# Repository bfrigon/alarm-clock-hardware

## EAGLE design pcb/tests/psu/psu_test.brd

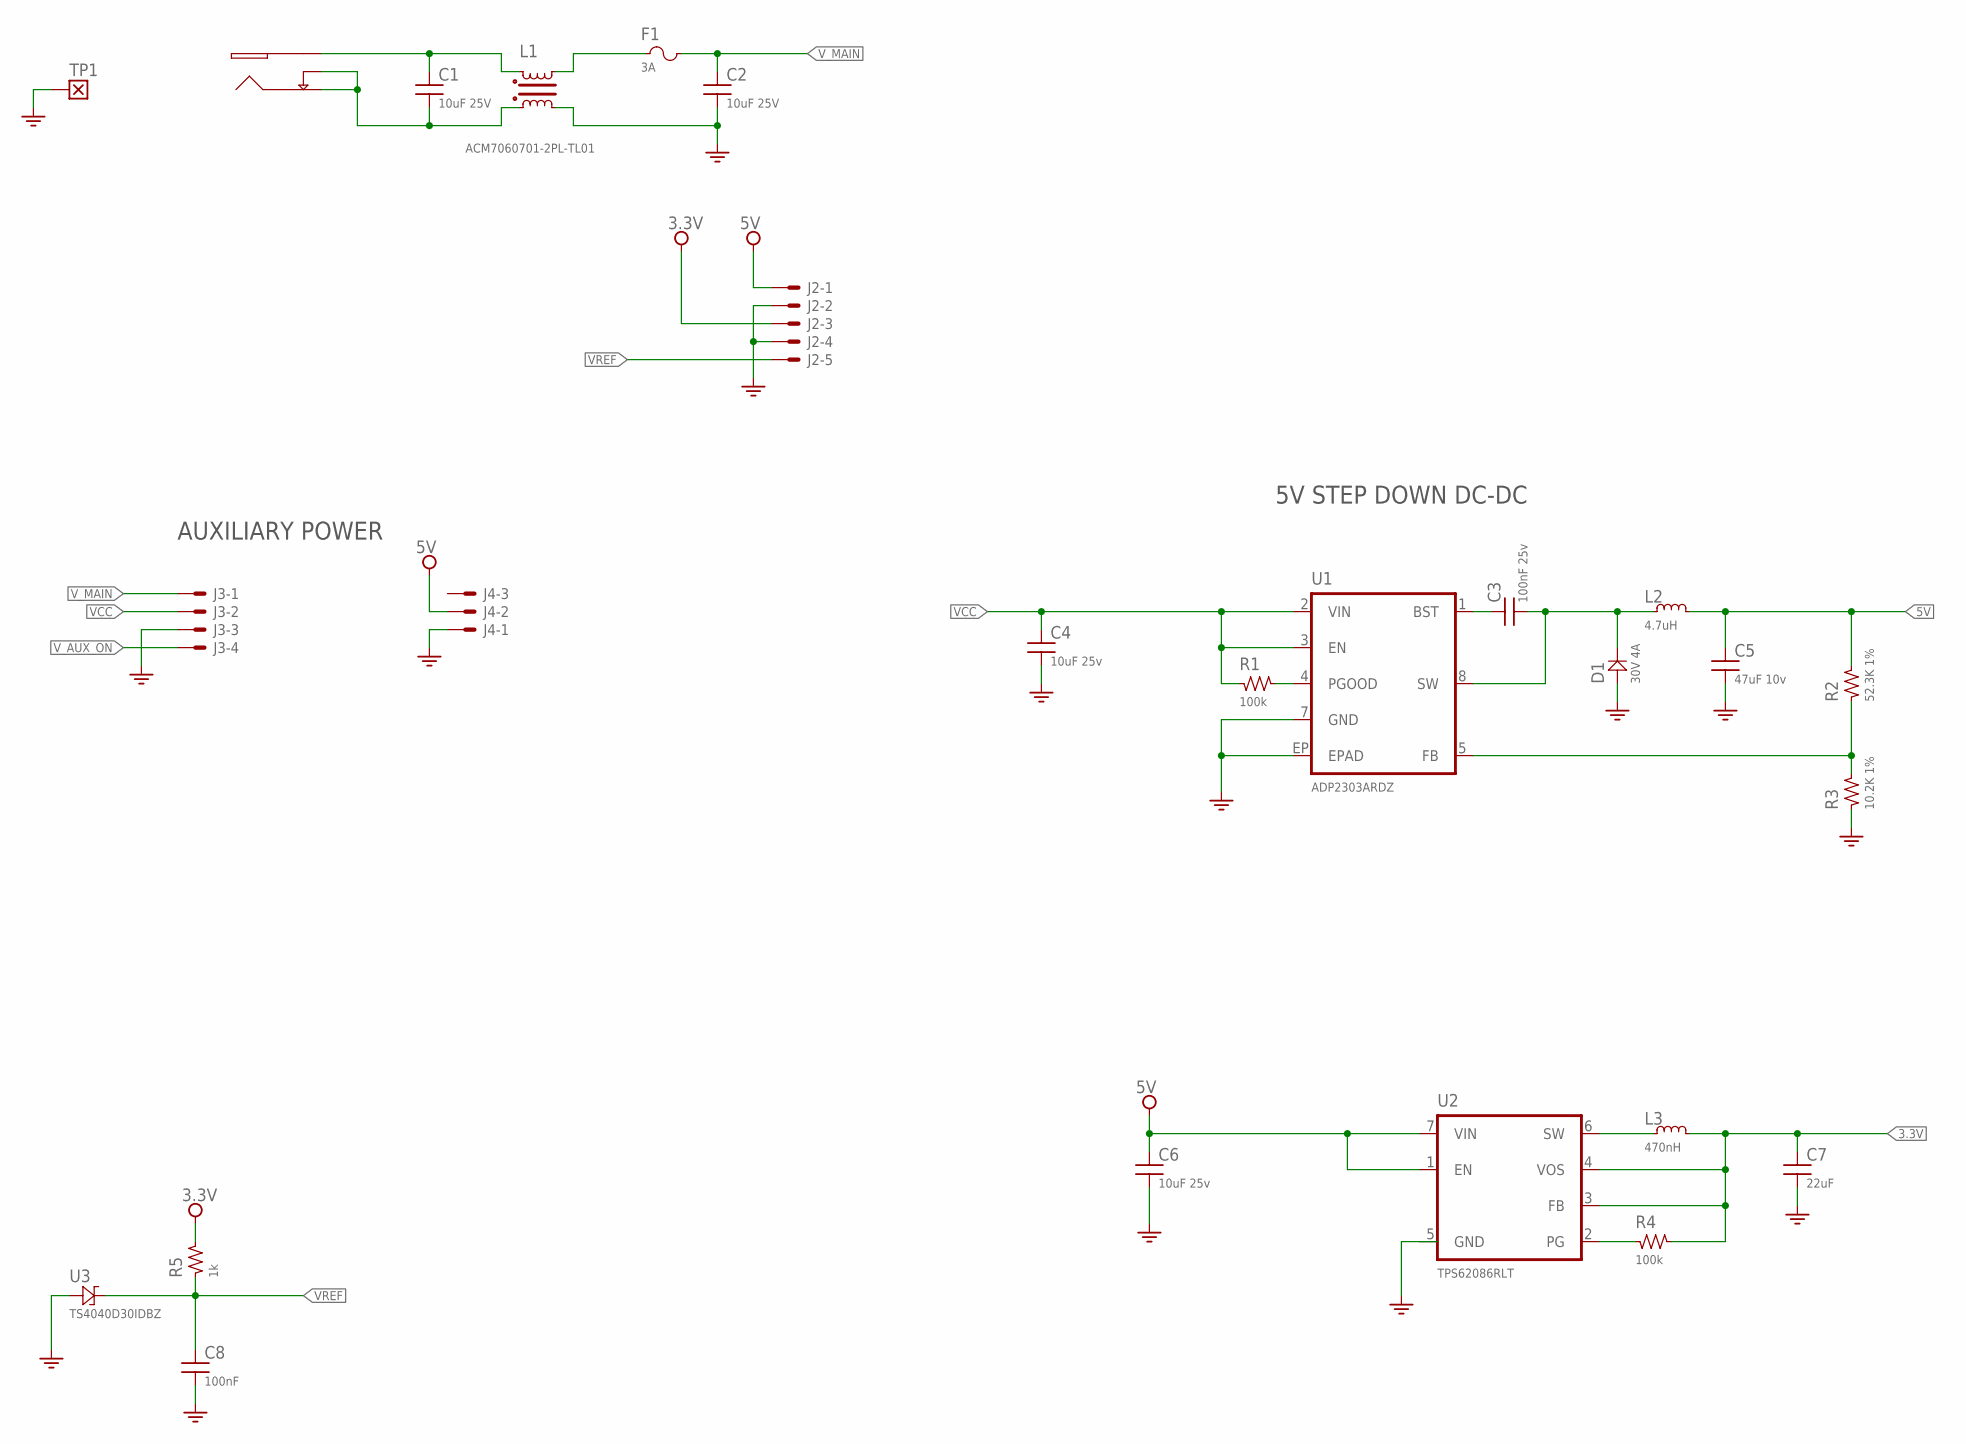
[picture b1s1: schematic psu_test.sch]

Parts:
C1, C2: 10uF 25V; SMD_0805
C3: 100nF 25v; SMD_0603
C4, C6: 10uF 25v; SMD_1206
C5: 47uF 10v; SMD_1206
C7: 22uF; SMD_1206
C8: 100nF; SMD_0603
D1: 30V 4A; DIODE_DO214-AA; PART_NO SSB43L-E3/52T
F1: 3A; SMD_1206
J1: CUI-PJ-013C
J2: SNG-100-HEADER-05-HDR-V; HDR_M_5
J3: SNG-100-HEADER-04-HDR-V; HDR_M_4
J4: SNG-100-HEADER-03-HDR-V; HDR_M_3
L1: ACM7060701-2PL-TL01; ACM7060; PART_NO ACM7060-701-2PL-TL01
L2: 4.7uH; IND_4020; PART_NO CLF10040T-4R7N
L3: 470nH; IND_4045
R1, R4: 100k; SMD_0603
R2: 52.3K 1%; SMD_0603
R3: 10.2K 1%; SMD_0603
R5: 1k; SMD_0603
TP1: TEST_POINT-TP_75X75; TP_75X75
U1: ADP2303ARDZ; SOIC8-EP
U2: TPS62086RLT; QFN-7
U3: TS4040D30IDBZ; SOT23

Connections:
3.3V: C7.1, J2.3, L3.2, R4.2, R5.2, U2.3 (FB), U2.4 (VOS)
5V: C5.1, C6.1, J2.1, J4.2, L2.2, R2.2, U2.1 (EN), U2.7 (VIN)
GND: C2.2, C4.2, C5.2, C6.2, C7.2, C8.2, D1.A, J2.2, J2.4, J3.3, J4.1, L1.OA, R3.1, TP1.1, U1.7 (GND), U1.EP (EPAD), U2.5 (GND), U3.2 (A)
unnamed: C1.2, J1.2 (GND), J1.3 (SW), L1.IA
unnamed: R1.2, U1.4 (PGOOD)
unnamed: C1.1, J1.1 (V+), L1.IB
unnamed: C3.1, U1.1 (BST)
unnamed: F1.1, L1.OB
unnamed: C3.2, D1.K, L2.1, U1.8 (SW)
unnamed: R2.1, R3.2, U1.5 (FB)
unnamed: L3.1, U2.6 (SW)
unnamed: R4.1, U2.2 (PG)
VCC: C4.1, J3.2, R1.1, U1.2 (VIN), U1.3 (EN)
VREF: C8.1, J2.5, R5.1, U3.1 (K)
V_AUX_ON: J3.4
V_MAIN: C2.1, F1.2, J3.1

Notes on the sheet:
5V STEP DOWN DC-DC
AUXILIARY POWER

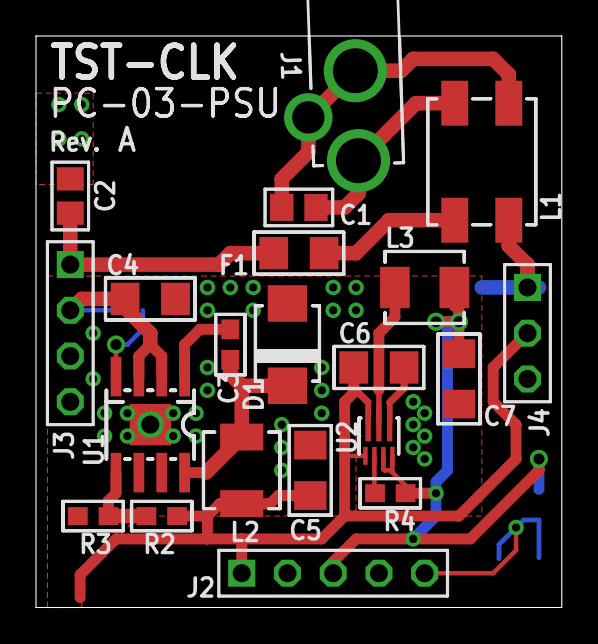
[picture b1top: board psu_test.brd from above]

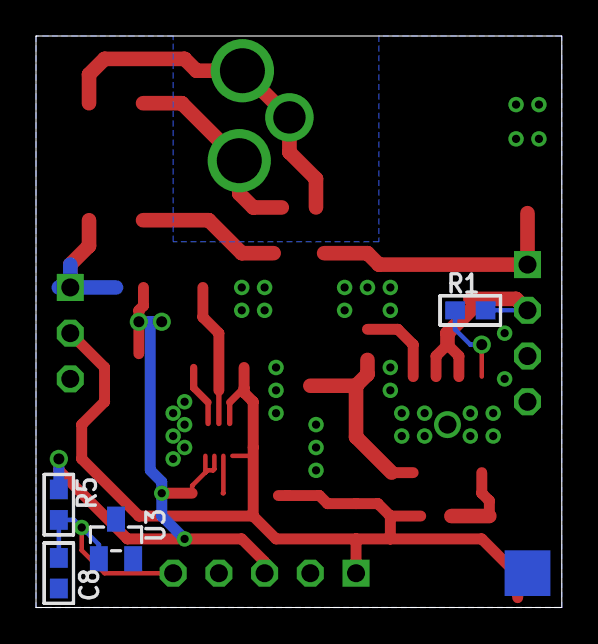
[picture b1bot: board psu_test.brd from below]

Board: 2 copper layers, 29.2 x 31.8 mm, 27 parts (5 on the bottom side), 15 nets.

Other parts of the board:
U$1: INFO_COMPACT

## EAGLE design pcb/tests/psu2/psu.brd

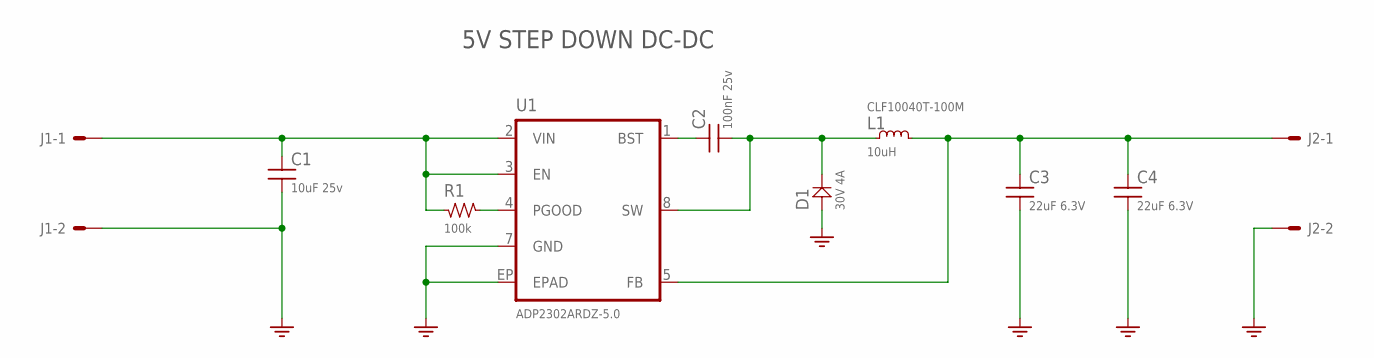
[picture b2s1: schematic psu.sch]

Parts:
C1: 10uF 25v; SMD_1206
C2: 100nF 25v; SMD_0603
C3, C4: 22uF 6.3V; SMD_1206
D1: 30V 4A; DIODE_DO214-AA
J1, J2: SNG-100-HEADER-03-HDR-V; HDR_M_3
L1: 10uH; IND-10X10; PART_NO CLF10040T-100M
R1: 100k; SMD_0603
U1: ADP2302ARDZ-5.0; SOIC8-EP

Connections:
5V: C3.1, C4.1, J2.1, L1.2, U1.5 (FB)
GND: C1.2, C3.2, C4.2, D1.A, J1.2, J2.2, U1.7 (GND), U1.EP (EPAD)
unnamed: R1.2, U1.4 (PGOOD)
unnamed: C2.1, U1.1 (BST)
unnamed: C2.2, D1.K, L1.1, U1.8 (SW)
VCC: C1.1, J1.1, R1.1, U1.2 (VIN), U1.3 (EN)

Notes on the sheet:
5V STEP DOWN DC-DC

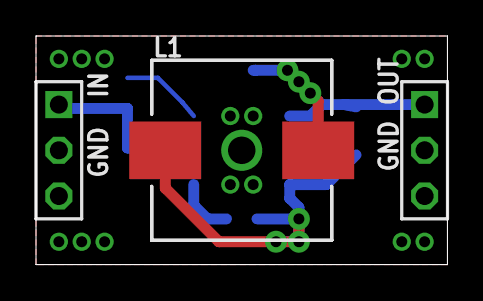
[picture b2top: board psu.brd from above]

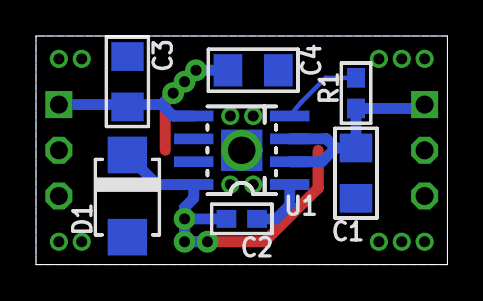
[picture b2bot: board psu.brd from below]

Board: 2 copper layers, 22.9 x 12.7 mm, 10 parts (7 on the bottom side), 6 nets.
